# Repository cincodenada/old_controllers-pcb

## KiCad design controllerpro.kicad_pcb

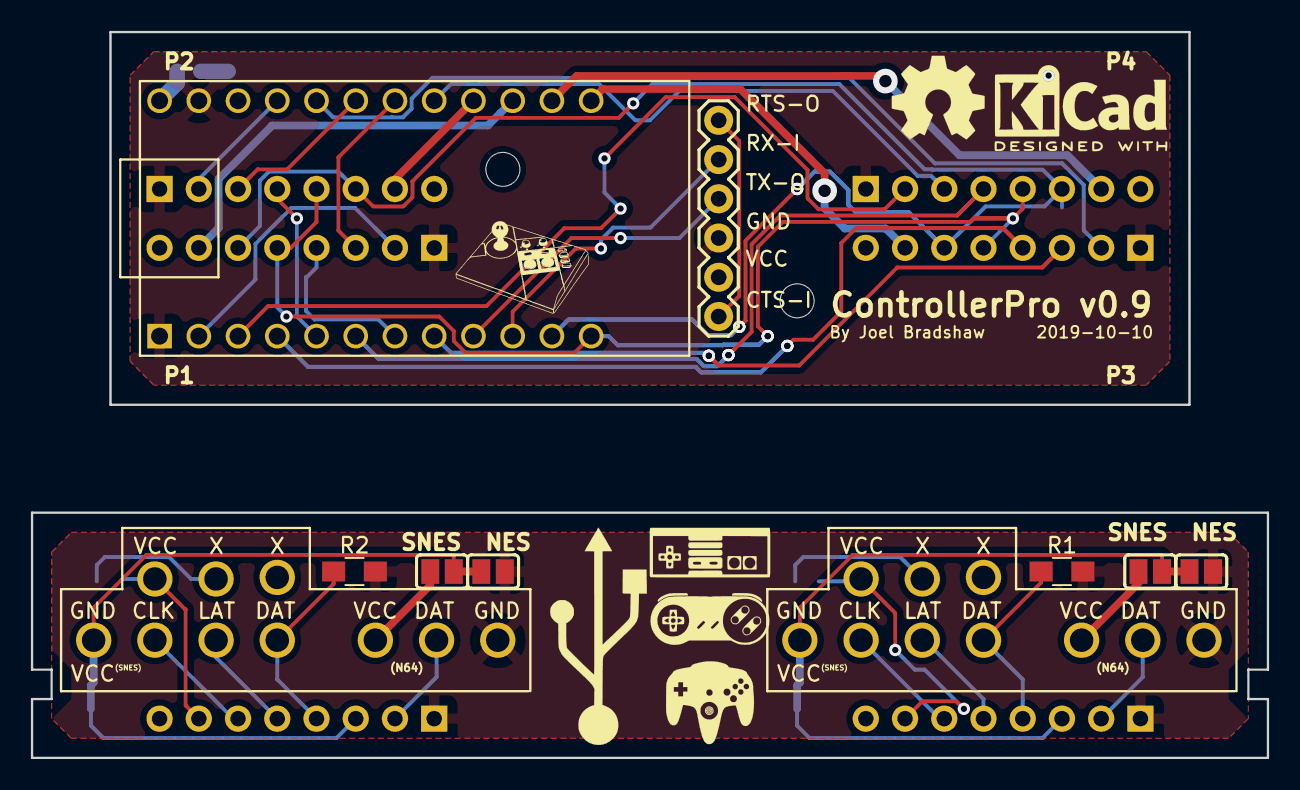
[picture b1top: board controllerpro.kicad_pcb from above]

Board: 2 copper layers, 80.0 x 47.0 mm, 21 parts (0 on the bottom side), 40 nets.

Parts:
JP1, JP3, JP4, JP6, JP7, JP8, JP9: SolderJumper_2_Open; SOLDERJUMPER
JP2, JP5: SolderJumper_2_Bridged; SOLDERJUMPER
P1, P2: Conn_01x08_Male; PinHeader_1x08_P2.54mm_Vertical
R1, R2: 10k; R_0805_HandSoldering
S1, S2, S3, S4: Conn_01x08_Female; Socket_Strip_Angled_1x08_Pitch2.54mm
U1: Teensy3.2; Teensy30_31_32_LC
U2: RN42
U3, U4: NINTENDO-MULTI_LARGE; NINTENDO-MULTI

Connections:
/BT_RX: U1.10, U2.RX-I
/BT_TS: U2.CTS-I, U2.RTS-0
/BT_TX: U1.9, U2.TX-0
/CLOCK: S1.6, S2.6, S3.6, S4.6, U1.11
/Child Board/CLK_A: P2.6, U3.2
/Child Board/CLK_B: P1.6, U4.2
/Child Board/ENABLE_A: JP8.1, P2.7, U3.10
/Child Board/ENABLE_B: JP9.1, P1.7, U4.10
/Child Board/FAST_DATA_A: P2.2, U3.6
/Child Board/FAST_DATA_B: P1.2, U4.6
/Child Board/LATCH_A: P2.5, U3.3
/Child Board/LATCH_B: P1.5, U4.3
/Child Board/SLOW_DATA_A: P2.4, R1.1, U3.4
/Child Board/SLOW_DATA_B: P1.4, R2.1, U4.4
/Child Board/S_OR_NES_A: JP2.1, JP2.2, JP3.2, JP4.1, P2.3, U3.1
/Child Board/S_OR_NES_B: JP5.1, JP5.2, JP6.2, JP7.1, P1.3, U4.1
/LATCH: S1.5, S2.5, S3.5, S4.5, U1.12
ENABLE1: S1.7, U1.24
ENABLE2: S2.7, U1.25
ENABLE3: S3.7, U1.22
ENABLE4: S4.7, U1.23
FAST_DATA1: S1.2, U1.2
FAST_DATA2: S2.2, U1.30
FAST_DATA3: S3.2, U1.29
FAST_DATA4: S4.2, U1.3
GND: S1.1, S2.1, S3.1, S4.1, U1.1, U1.32, U2.GND
GNDA: JP4.2, JP7.2, P1.1, P2.1, R1.2, R2.2, U3.7, U4.7
unnamed: JP1.2, U1.33
unnamed: JP8.2, U3.9
unnamed: JP9.2, U4.9
SLOW_DATA1: S1.4, U1.7
SLOW_DATA2: S2.4, U1.5
SLOW_DATA3: S3.4, U1.4
SLOW_DATA4: S4.4, U1.6
S_OR_NES1: S1.3, U1.27
S_OR_NES2: S2.3, U1.28
S_OR_NES3: S3.3, U1.8
S_OR_NES4: S4.3, U1.26
VCC: JP1.1, S1.8, S2.8, S3.8, S4.8, U1.31, U2.VCC
VCCA: JP3.1, JP6.1, P1.8, P2.8, U3.5, U4.5

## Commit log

2013-08-09 Initial layout and such
2013-08-15 Now smaller! Rearranged things to minimize size
    Mostly to reduce board cost, but hey!
2013-08-15 Add my custom teensy parts to the custom library
    Just removed the unneeded pins, we'll just be using two headers
2013-08-17 Widening power traces, adding alignment check vias
2013-09-07 Adding some net names, connecting a missing GND
2013-09-21 Add OpenSCAD model
2013-09-21 Expanding, layout 1
2013-09-21 Expanding, layout 2 (2x2) (1.525x3.275)
2013-09-21 Updated OpenSCAD model
2013-09-21 Working on 2x2 board with teensy straddling N64
2013-09-21 Using only needed pins, also starting on wires
2013-09-21 Using only needed pins
2013-09-21 Teensy in the middle of 2x2 (rotated)
2013-09-21 All wired up (intially)!
2013-09-21 Hiding layout bits, starting on actual box
2013-09-21 Expanding via mirroring every other controller
2013-09-22 Trying to actually line up box with board
2013-09-22 Rerouting some stuff to shrink and center board
    Updating model with new board dimensions and finishing
    re-specfiying controller positions. Yay!
2013-09-26 Adding pull-up resistors
2013-09-26 Conforming box model to actual board, and adding pins
2013-09-26 Moving controllers father away from the teensy
    Avoiding socket collisions per model
2013-09-26 Adding some images/renders
2013-09-26 Fixing images because OpenSCAD can't render properly
2013-09-29 Finishing moving controller ports closer together
    Also added plugin spot on model
2013-09-29 Separate connector-top thing out
2013-09-29 Refactoring things a good bit
    Extracting bits of code into sensible files
2013-09-29 Adding holders to the model
    Gonna run into socket problems though...hmm.
2013-09-29 Re-working the top/bottom grabbers a little
2013-09-30 Fixing the bothsides() function
2013-09-30 Tweaking and adding clickers to the holders
2013-10-06 Adding extra headers to the teensy
    Also tweaking board width
    And adding detail to headers (for printing just sockets)
2013-10-08 Converting to mm, redoing some measurements
    Now I have actual calipers!
2013-10-08 Adding some datasheets and generated STLs
2013-10-08 Updating NES/SNES controller definitions
    Now they actually use my measurements...
2013-10-16 Reworking the top/bottom halves, filling in socket gaps
    Moving to half/half to work around socket walls.
    Lots of reworking of the Teensy socket,
    also adjusting for Teensy pin offset
    which might be troublesome
2013-11-17 Flipping the extra pins, adding board module
    Also fixed linenum script (maybe) and added animation stuff
2013-11-17 Updating STLs
2013-11-18 Making connector cutout wall thicker
    Also adding feet to the bottom and updating STLs
2013-12-30 Adding silkscreens, finalizing for OSH Park
2013-12-31 Flipping Teensy...argh
2013-12-31 Updating rev info
2014-08-07 Shorten bottom sides to make room for the top piece
2014-08-07 Add some clearances
2014-08-07 Add some clearance, and do more fudging
    Also separate out the fudging from the actual values
2014-11-06 Remove IC switches, just use two lines from the µc
2014-11-13 Post-rebase cleanup of boardfile
2014-11-13 Update version date
2014-11-14 Rename ports, add silkscreen port numbers
2014-11-14 Add QR code
2014-11-14 Fix 3
2014-11-14 Update date and move up a bit
2014-11-17 pin_base -> pin_base_height
2014-11-17 Greatly simplify grabbers
2014-11-17 Add board_top helper variable
    Seriously, why did I not do this yet
2014-11-17 Make Teensy push the ceiling up if need be
    And use socket_thick so pin_gap is actually accurate
    Had to rework the connector_cap a good bit, it's a bit awkward now
    but should work fine
2014-12-13 Move box top down, generalize both* functions
2015-08-02 Update board for Bluetooth module
2015-08-02 Connect bluetooth power, etc:
2015-09-07 Switch VCC to 3.3v
    Remove VREG, supply NES/SNES and N64 all with 3.3v
2015-09-07 Do some basic simplifications afforded by 3.3V switch
2015-09-07 Shrink drills for controller pins
2015-09-07 Tighten up keepout lines for pins
2015-09-07 Rework wires on right side for BT antenna
    With new space between pins, we can rearrange a bit
    And completely clear out the space under the BT antenna
2015-09-07 Remove pull-up resistors for N64
    Not necessary any more now that Teensy is at 3.3v
2015-09-07 Some further simplifications/improvements
    Mainly better connecting the ground/power planes
2015-09-07 Update RN42 and move to our custom lib
    Get the footprint/silkscreen on the right side and things
2015-09-07 Update version number and date
2015-09-07 Fix layers for port pins
2015-09-07 Actually, move all pins to tDocu layer
    Shouldn't be silkscreened, consistent with other packages
2018-03-31 Initial commit from import
2018-03-31 Align board to grid, add border for small board
2018-03-31 Add headers, lots of rearranging/tidying
2018-03-31 Shorted connectors to test connectivity
2018-03-31 Revert "Shorted connectors to test connectivity"
    This reverts commit bff4c321492e34593da7785c8a90028fe11ea69b.
2018-04-01 Match footprints and re-label
2018-04-01 Move second set of multiports
2018-04-01 Start laying out board
2018-04-01 More layout
2018-04-01 Remove stray vcc labels
2018-04-01 Make it default to configurable SNES/NES
2018-04-01 Finish initial layout of first port
2018-04-01 Fix port numbers
    That was annoying, but fine
2018-04-01 Place remainder of big footprints
    Resistors still to do
2018-04-01 Clear out existing tracks
2018-04-01 Connect first two terminals (the easy ones)
2018-04-01 Initial complete connection
2018-04-01 Scootch the connectors closer
    They're the constraining factor here
2018-04-01 First attempt at shrinking board
2018-04-01 Tie up loose ends from shrinking board
2018-04-01 Fix misalignment/non-centering of pins
2018-04-01 Add keepout for bluetooth
2018-04-01 Make daughterboards smaller
2018-04-01 Attempt to add zones to daughterboard
2018-04-01 Work on zones on daughterboards
    Still some figuring to do
2018-04-08 Update headers with actual footprint
2018-04-08 Update resistor placement
2018-04-08 Import solder jumpers from Teensy
    Better than caps/resistors
2018-04-08 Set up DRCs for OSHPark
2018-04-08 Move measurements to Dwg layer
    WTF silkscreens
2018-04-08 Switch Teensy package
2018-04-08 Fix pins on new Teensy
2018-04-08 Update boardfile
2018-04-08 Fix board
2018-08-09 Remove duplicate board, add cutouts
2018-08-09 Update to new libraries and fix buses
2018-08-09 Remove second board from schematic
2019-02-05 Add pulldown resistors, shrink child board
2019-02-05 Switch to Teensy 3.2 footprint
2019-02-05 More 3.2 adjustments
    Make it Teensy2 compatible even, hopefully!
2019-02-05 Switch to solder bridges for the SNES mode selectors
2019-02-06 Make controller pin holes smaller
    Finally found a datasheet that recommends a reasonable size
2019-02-06 Shrink top board considerably
    So much empty space!
2019-02-06 Make the bottom board smaller!
    SMALLER SMALLER SMALLER
2019-02-06 Silkscreen!!
    Logos! Labels!
2019-02-08 Nudge bluetooth, refining silkscreen/labels
2019-02-18 Fixes from hardware debugging
    Connect daughterboards to ground (!)
2019-02-18 Split LATCH into four
    Also fix misplaced NES VCC (!!) and ports
2019-02-18 Make power traces thicker
2019-03-14 More tidying
2019-03-14 Manually rename ports
    Also match board by timestamp, nice!
    perl -p -i -e 's/\b(PORT|S|P|5VDATA|3VDATA|S_OR_NES|LATCH)1\b/${1}4/g' *
    perl -p -i -e 's/\b(PORT|S|P|5VDATA|3VDATA|S_OR_NES|LATCH)2\b/${1}1/g' *
    perl -p -i -e 's/\b(PORT|S|P|5VDATA|3VDATA|S_OR_NES|LATCH)3\b/${1}2/g' *
    perl -p -i -e 's/\b(PORT|S|P|5VDATA|3VDATA|S_OR_NES|LATCH)0\b/${1}3/g' *
    perl -p -i -e 's/\b(PORT|S|P|5VDATA|3VDATA|S_OR_NES|LATCH)\[0..3\]/${1}[1..4]/g' *
2019-03-14 Re-add silkscreens
2019-03-15 Silkscreen tweaks
2019-03-15 Fix a needlessly squiggly trace
2019-08-03 Add missing library
2019-08-03 Add a couple more measurements
2019-08-03 Add child board heirarchical sheet
2019-08-04 Move back to one latch, instead try current detect
2019-08-04 Fix connector orientation, get rid of tabs
2019-08-04 Move RN42 board
    It's on top which is great but needs to be out from under the Teensy
2019-08-04 Switch S_OR_NES and DETECT
    So we can do analog measurements on DETECT
    Abandon running wider lines for these, it'll probably be fine
2019-08-05 Connect AGND
2019-08-05 Rename a bunch of stuff, switch DETECT back
2019-08-05 Move things around so everything that needs touch has it
2019-08-09 Fix the board up after moving all the pins around
2019-08-09 Fuck the schematic all up
2019-08-09 Start repairs
2019-08-09 Finish reworking all the things
2019-08-09 Use local labels instead of global and add NCs
2019-08-09 I don't even know what I did this time
2019-08-09 Silkscreen updates, tiny tweaks
2019-08-13 Add optional pulldown resistors
    Just in case, doesn't hurt to have 'em
2019-08-16 Make child boards flippable
    A little bigger, but hopefully only temporarily
2019-08-16 Connect remaining inputs to child boards
    They don't do anything yet, but why not futureify it
2019-08-17 Flip alternate headers
    Would have made the controllers upside-down again
2019-08-28 Initial rejiggering for 5V enable
2019-08-28 Rework connections on child boards only
2019-10-07 Update board
    I don't know why this didn't pick up the first time
2019-10-07 Add mounting holes, update to 0.8.2
2019-10-10 Update silkscreens
2019-10-10 Don't connect extra VCC by default
2019-10-11 Fix mapping and ports
    God, what a mess
2019-10-11 Make trace less circuitous
2019-10-11 Make version 0.9
    We've changed enough here
2019-10-11 Tidy up refs
2019-10-24 Initial building docs
    Seeing if this shows up like I want it to
2019-10-24 Fix headers and image paths
2019-10-24 Add the rest of the docs and a buncha images
2019-10-24 Fix some words
2019-10-24 More image updates
2019-10-24 More typos, fix order of clips, rotate overhang
2019-10-25 Text updates, add link to STL for jig
2019-10-26 Add firmware info
2019-10-26 page
2019-10-28 Link to GitHub release instead of awkward Hackster
2021-11-14 Add .gitignore and logos

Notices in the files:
parts and their libraries:
Copyright 2016 Accelerated Designs. All rights reserved.
